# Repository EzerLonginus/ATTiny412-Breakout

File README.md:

# ATTiny412-Breakout
Simple breakout for the ATTiny412 using USB for uploading and serial comms

This board is a simple breakout for the ATTiny412.  This allows for programming and UART serial communications through a USB interface.  Included in breakout is a power led indication, and a few feedback LEDs for UART and UPDI programming.  UPDI and UART need to be selected via switch on the front of the breakout.

## Purpose
I wanted a way to quickly and easily test some software with the attiny412 (or similar avr chip), and not have to have a programmer and separate power source connected to chip.  This usually involved using a USB connector for power (sometimes doubling as a serial comms port) and some UPDI programmer to upload code.  This board will hopefully just allow me to use the USB for all functionality and to make development a little be cleaner and easier. 

## Scematic

## Layout

## 3D Render

## Current State of Affairs
### Version 1
* Populate and test board
* Fix the inevitable issue that I missed during production

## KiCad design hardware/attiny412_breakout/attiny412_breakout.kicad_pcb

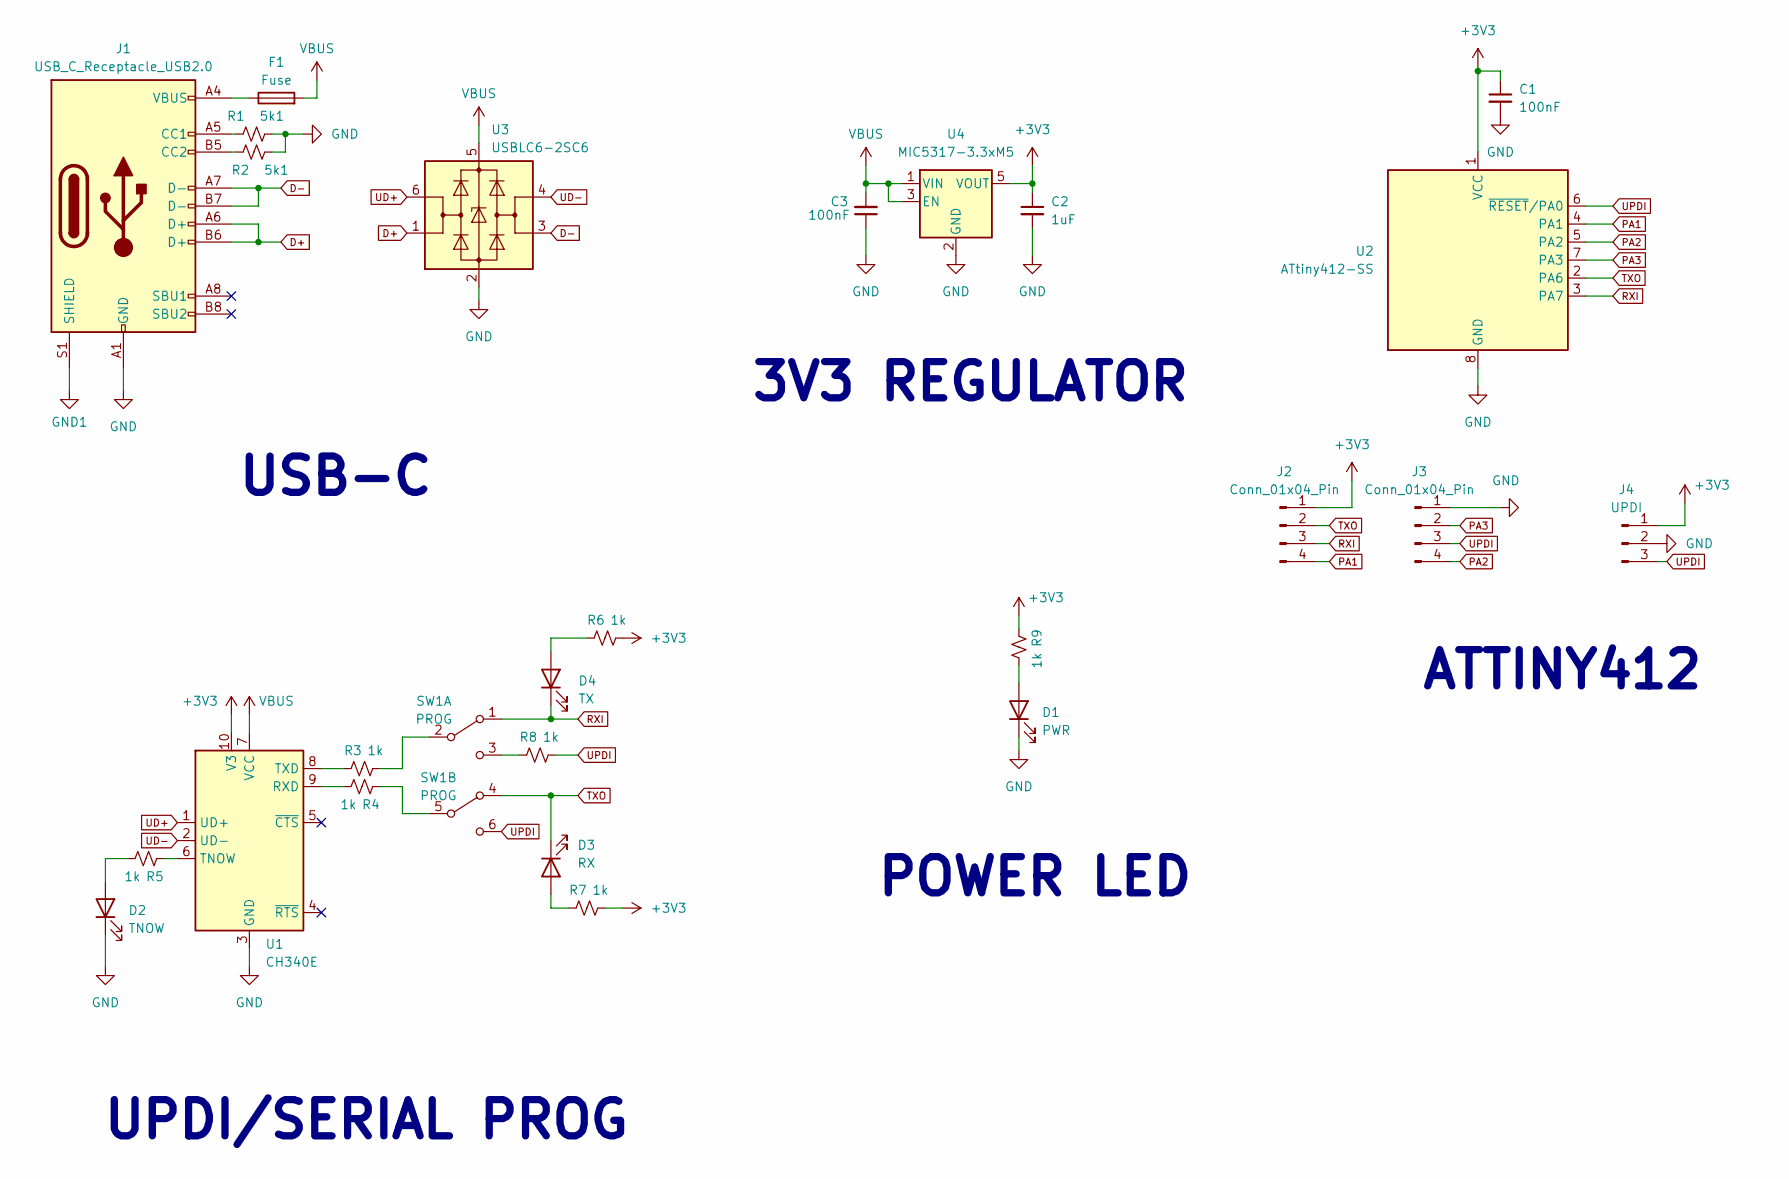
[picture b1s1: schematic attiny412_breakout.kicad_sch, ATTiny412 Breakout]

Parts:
C1, C3: 100nF; C_0603_1608Metric
C2: 1uF; C_0603_1608Metric
D1: PWR; LED_0603_1608Metric
D2: TNOW; LED_0603_1608Metric
D3: RX; LED_0603_1608Metric
D4: TX; LED_0603_1608Metric
F1: Fuse; Fuse_0603_1608Metric
J1: USB_C_Receptacle_USB2.0; USB_C_Receptacle_G-Switch_GT-USB-7010ASV
J2, J3: Conn_01x04_Pin; PinHeader_1x04_P2.54mm_Vertical
J4: UPDI; 1x3_2.54mm_pin_staggered
R1, R2: 5k1; R_0603_1608Metric
R3, R4, R5, R6, R7, R8, R9: 1k; R_0603_1608Metric
SW1: PROG; SMD DPDT Toggle SS-3235S-L1
U1: CH340E; MSOP-10_3x3mm_P0.5mm
U2: ATtiny412-SS; SOIC-8_3.9x4.9mm_P1.27mm
U3: USBLC6-2SC6; SOT-23-6
U4: MIC5317-3.3xM5; SOT-23-5

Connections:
+3V3: C1.1, C2.1, J2.1, J4.1, R6.2, R7.2, R9.1, U1.10 (V3), U2.1 (VCC), U4.5 (VOUT)
D+: J1.A6 (D+), J1.B6 (D+), U3.1 (I/O1)
D-: J1.A7 (D-), J1.B7 (D-), U3.3 (I/O2)
GND: C1.2, C2.2, C3.1, D1.1 (K), D2.1 (K), J1.A1 (GND), J1.A12 (GND), J1.B1 (GND), J1.B12 (GND), J3.1, J4.2, R1.2, R2.2, U1.3 (GND), U2.8 (GND), U3.2 (GND), U4.2 (GND)
GND1: J1.S1 (SHIELD)
unnamed: D1.2 (A), R9.2
unnamed: D2.2 (A), R5.2
unnamed: D3.2 (A), R7.1
unnamed: D4.2 (A), R6.1
unnamed: F1.1, J1.A4 (VBUS), J1.A9 (VBUS), J1.B4 (VBUS), J1.B9 (VBUS)
unnamed: J1.A5 (CC1), R1.1
unnamed: J1.B5 (CC2), R2.1
unnamed: R3.2, SW1.2 (B)
unnamed: R8.1, SW1.3 (C)
unnamed: R4.1, SW1.5 (B)
unnamed: R4.2, U1.9 (RXD)
unnamed: R5.1, U1.6 (TNOW)
unnamed: R3.1, U1.8 (TXD)
PA1: J2.4, U2.4 (PA1)
PA2: J3.4, U2.5 (PA2)
PA3: J3.2, U2.7 (PA3)
RXI: D4.1 (K), J2.3, SW1.1 (A), U2.3 (PA7)
TXO: D3.1 (K), J2.2, SW1.4 (A), U2.2 (PA6)
UD+: U1.1 (UD+), U3.6 (I/O1)
UD-: U1.2 (UD-), U3.4 (I/O2)
UPDI: J3.3, J4.3, R8.2, SW1.6 (C), U2.6 (~RESET/PA0)
VBUS: C3.2, F1.2, U1.7 (VCC), U3.5 (VBUS), U4.1 (VIN), U4.3 (EN)

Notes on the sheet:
ATTINY412
3V3 REGULATOR
POWER LED
USB-C
UPDI/SERIAL PROG

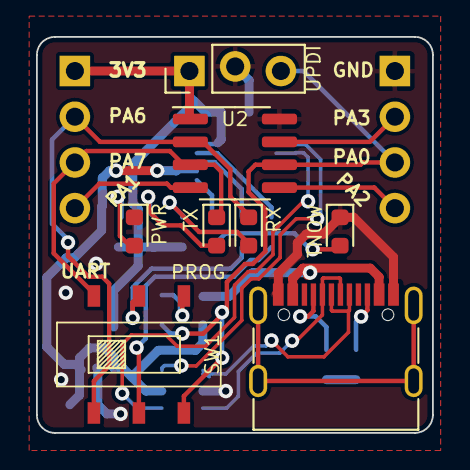
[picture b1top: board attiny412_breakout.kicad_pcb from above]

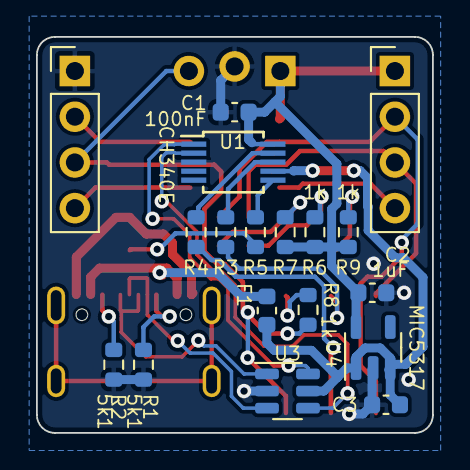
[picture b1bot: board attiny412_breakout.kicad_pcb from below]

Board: 2 copper layers, 22.0 x 22.0 mm, 26 parts (18 on the bottom side), 26 nets.
